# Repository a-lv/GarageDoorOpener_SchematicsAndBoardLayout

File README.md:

GarageDoorOpener_SchematicsAndBoardLayout
=========================================

Schematic and board layout for CadSoft EAGLE (www.cadsoftusa.com).

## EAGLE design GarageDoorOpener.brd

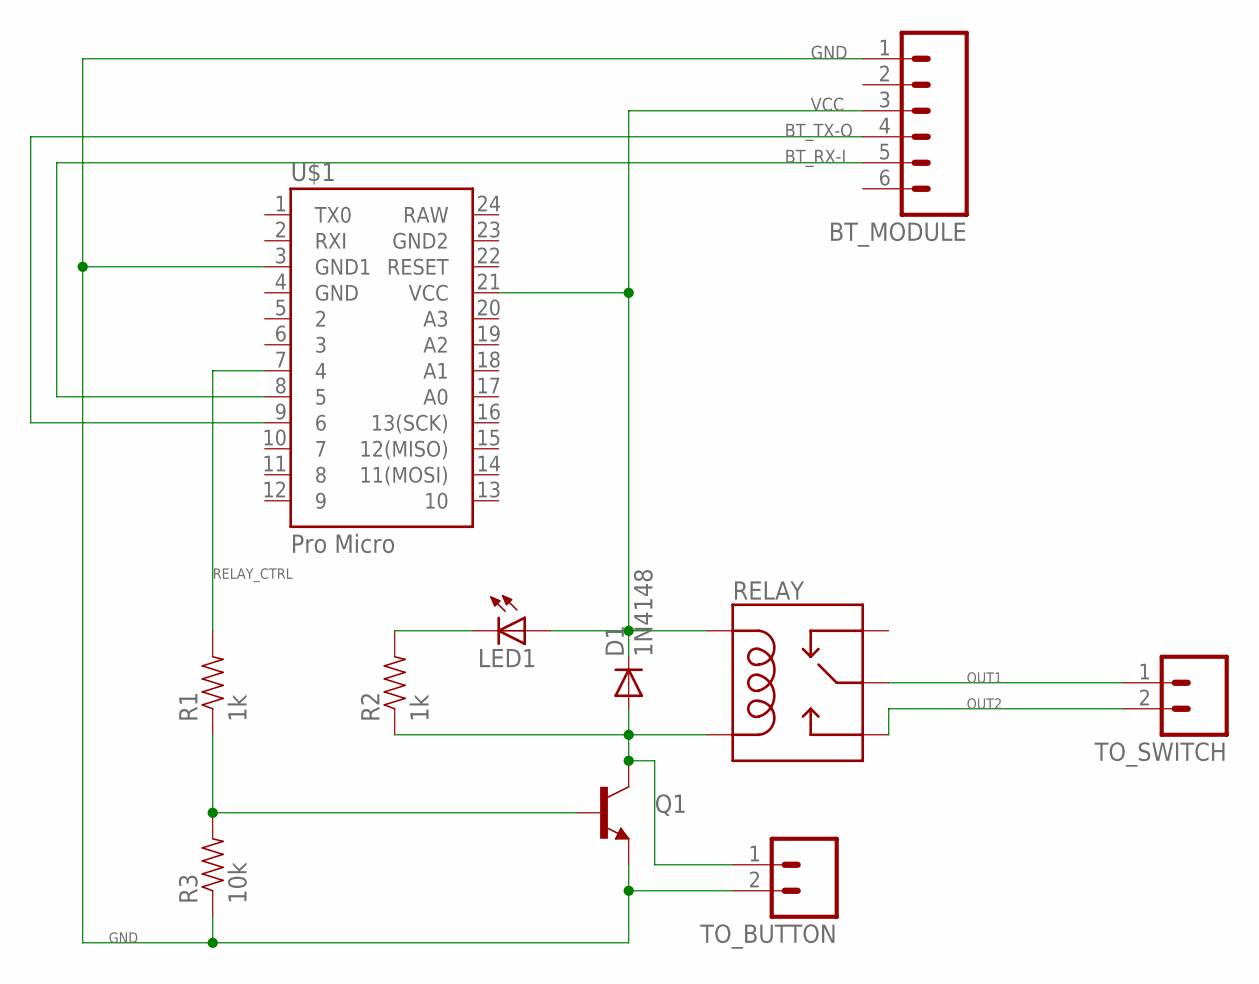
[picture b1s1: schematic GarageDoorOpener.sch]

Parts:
BT_MODULE: M06LOCK; 1X06_LOCK
D1: 1N4148; DIODE-1N4148
LED1: LED3MM
Q1: TRANSISTOR_NPNTO-92-AMMO; TO-92-AMMO
R1, R2: 1k; AXIAL-0.3
R3: 10k; AXIAL-0.3
RELAY: RELAYPTH4; RELAY-JZC
TO_BUTTON: M02LOCK; 1X02_LOCK
TO_SWITCH: M02-JST-2-PTH-NO_SILK; JST-2-PTH-NS
U$1: Pro Micro; ARDUINO_PRO_MICRO

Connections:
BT_RX-I: BT_MODULE.5, U$1.8 (5)
BT_TX-O: BT_MODULE.4, U$1.9 (6)
GND: BT_MODULE.1, Q1.1 (E), R3.P$1 (1), TO_BUTTON.2, U$1.3 (GND1)
unnamed: D1.A, Q1.3 (C), R2.P$1 (1), RELAY.1 (COIL2), TO_BUTTON.1
unnamed: Q1.2 (B), R1.P$1 (1), R3.P$2 (2)
unnamed: LED1.K (C), R2.P$2 (2)
OUT1: RELAY.4 (MAIN), TO_SWITCH.1
OUT2: RELAY.3 (NO), TO_SWITCH.2
RELAY_CTRL: R1.P$2 (2), U$1.7 (4)
VCC: BT_MODULE.3, D1.C, LED1.A, RELAY.5 (COIL1), U$1.21 (VCC)

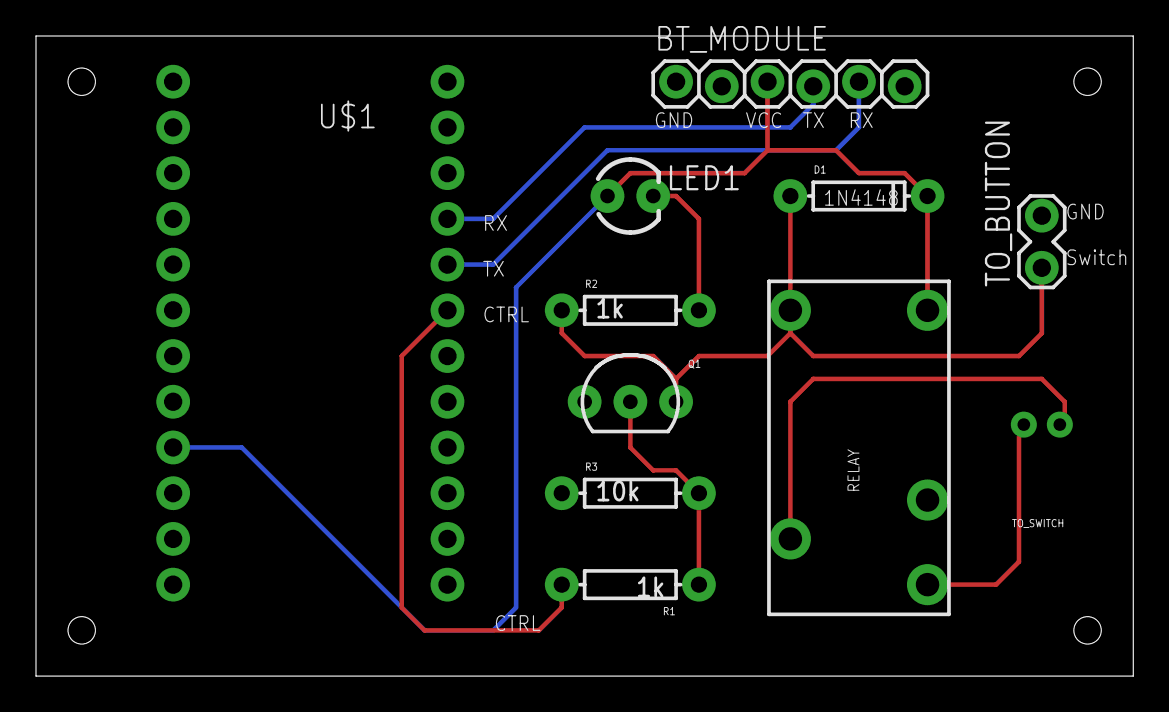
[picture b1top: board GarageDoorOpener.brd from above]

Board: 2 copper layers, 61.0 x 35.6 mm, 11 parts (0 on the bottom side), 10 nets.

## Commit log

2014-02-13 First committ
2014-02-14 Create README.md
    First commit of readme

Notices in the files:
parts and their libraries:
SparkFun-Electromechanical: Licensing: CC v3.0 Share-Alike You are welcome to use this library for commercial purposes.
